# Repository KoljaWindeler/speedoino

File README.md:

# speedoino
A DIY Speedometer with OLED Display, GPS, Bluetooth, etc
Please refer to www.speedoino.de

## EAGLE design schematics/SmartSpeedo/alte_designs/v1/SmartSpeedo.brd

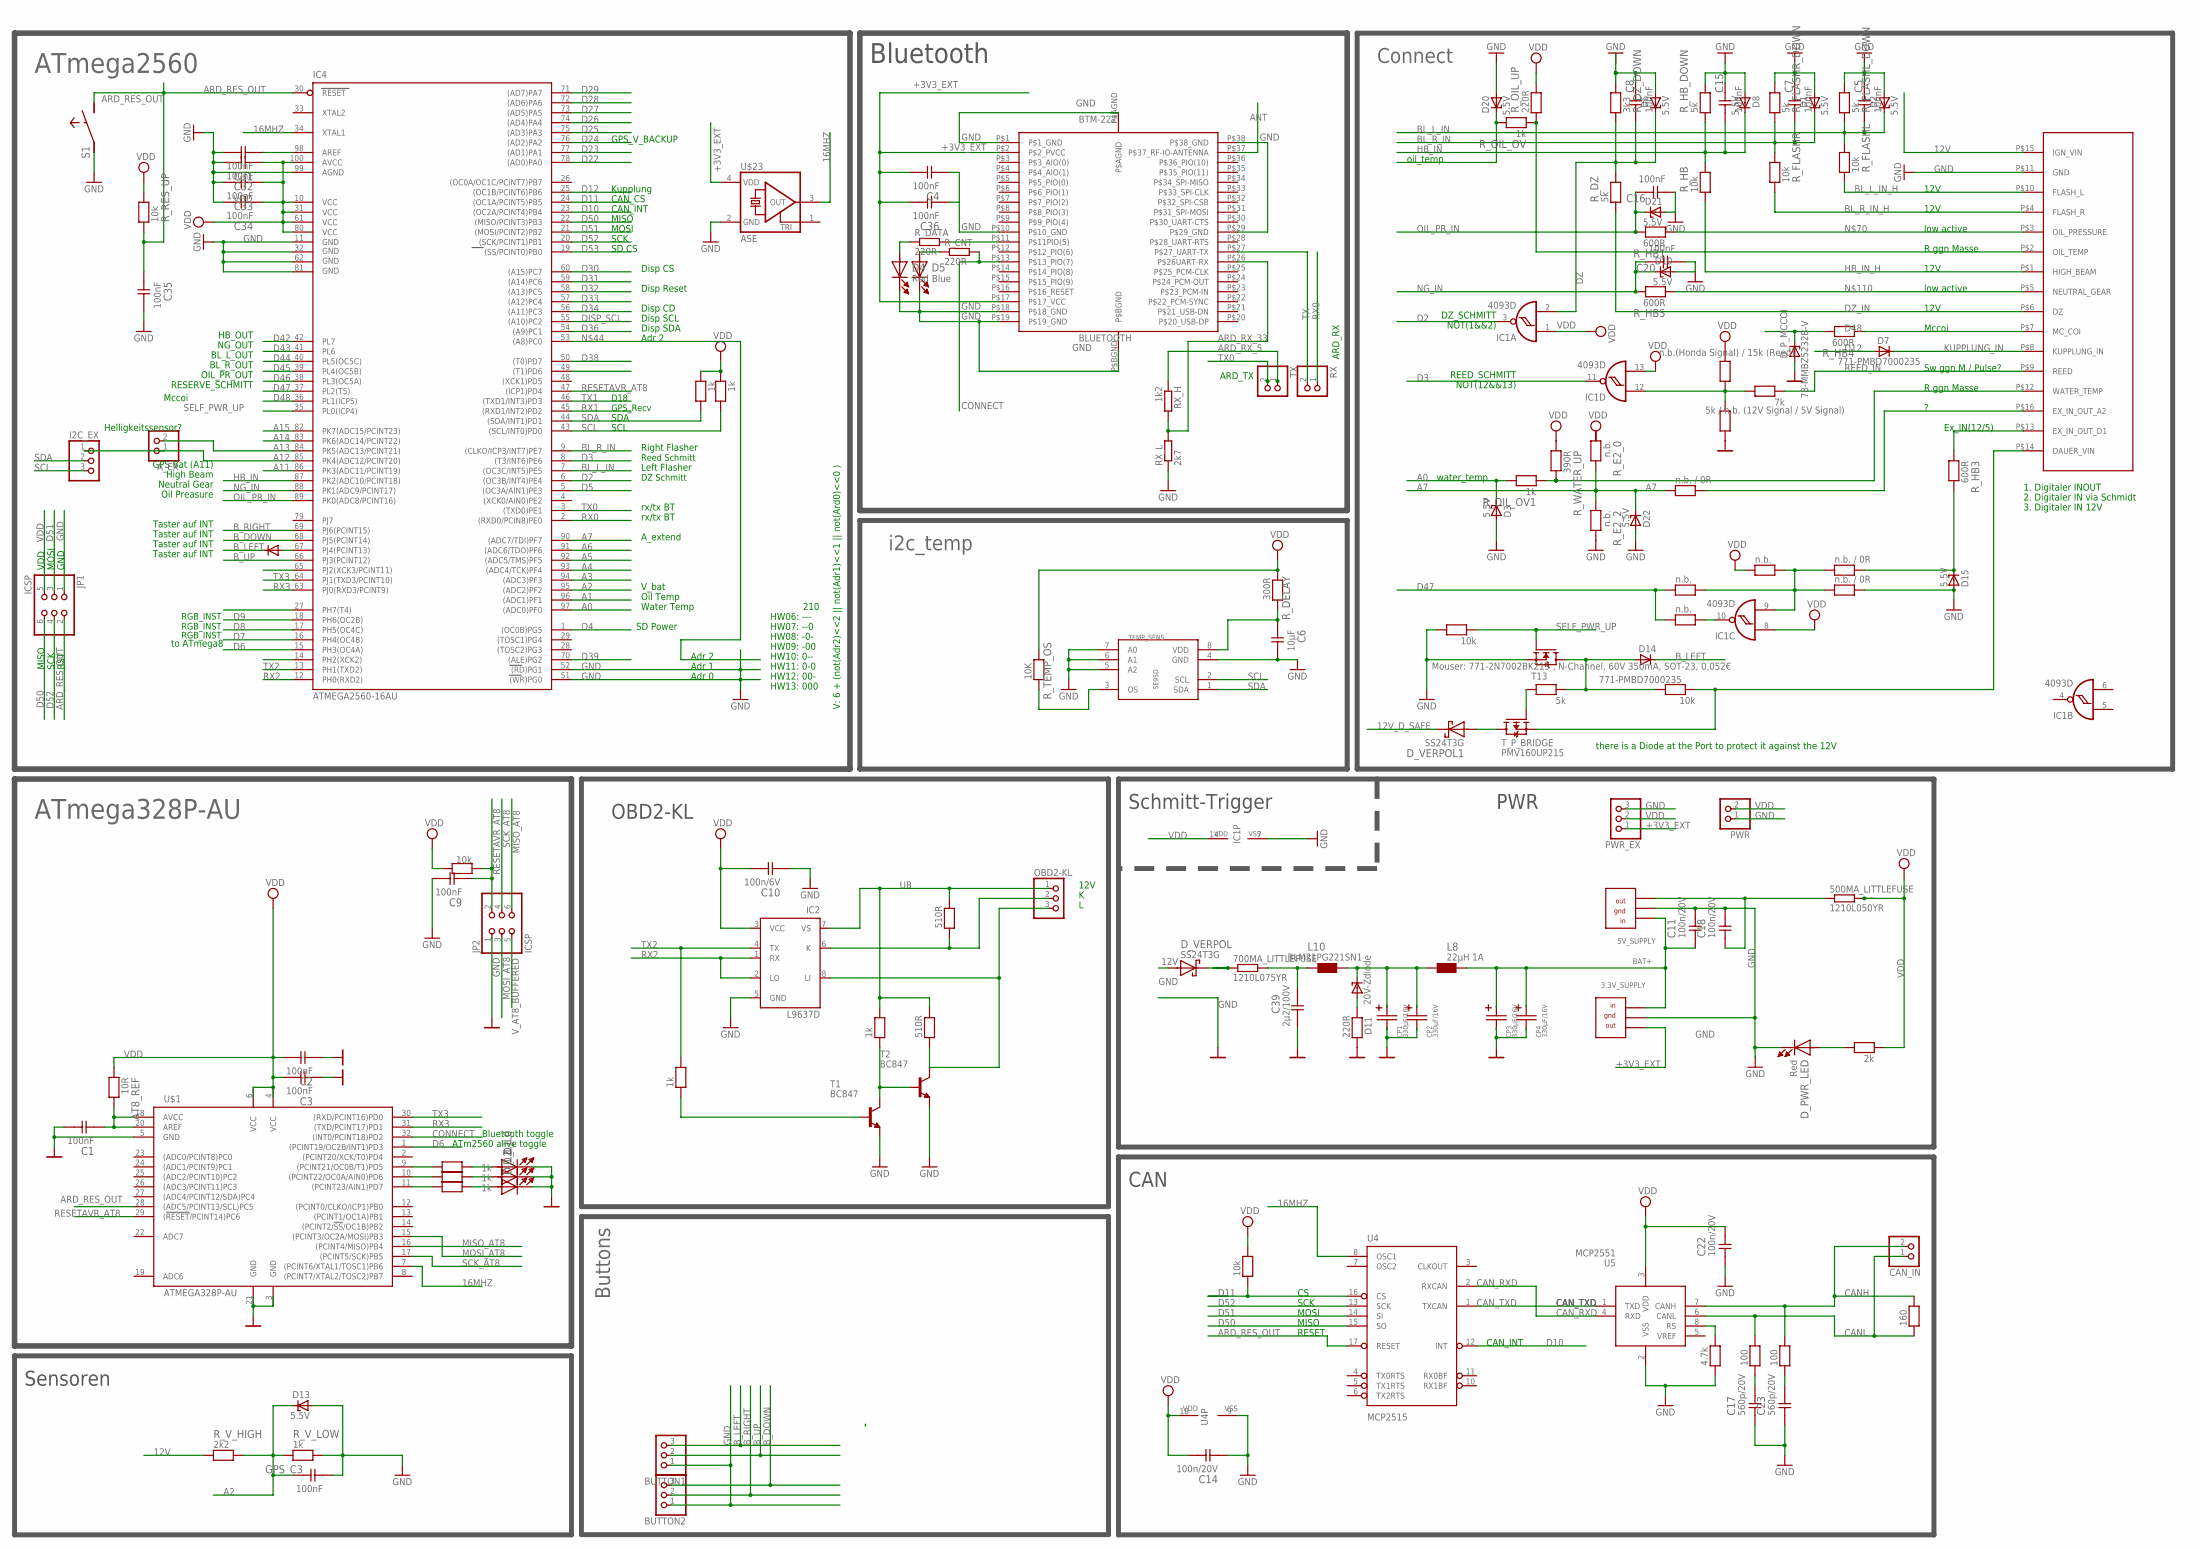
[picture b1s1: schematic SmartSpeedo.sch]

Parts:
3.3V_SUPPLY: OKI78SR3.31.5WHC; OKI-78SR
5V_SUPPLY: OKI78SR51.5W36HC; OKI-78SR
500MA_LITTLEFUSE: 1210L050YR; R1210
700MA_LITTLEFUSE: 1210L075YR; R1210
AT8_REF: 10R; 0805
A_EX: PINHD-1X2; 1X02
BLUETOOTH: BTM-222
BUTTON1, BUTTON2: PINHD-1X3; 1X03
C1, C2, C3, C4, C5, C7, C8, C9, C15, C16, C20, C31, C32, C33, C34, C35, C36: 100nF; 0805
C6: 10µF; 0805
C10: 100n/6V; 0805
C11, C14, C18, C22: 100n/20V; 0805
C17, C23: 560p/20V; 0805
C39: 2µ2/100V; 0805
CAN_IN: PINHD-1X2; 1X02
CP1, CP2, CP3, CP4: 330µF/16V; SMD/SMT_6.6/6.6
D1, D2, D3, D6, D8, D10, D13, D15, D20, D21, D22: 5.5V; SOT23
D4: Red; LED-0805
D5: Blue; LED-0805
D7, D12, D14: 771-PMBD7000235; SOT23
D11: 20V-Zdiode; SOT23
D_L0, D_L1, D_L2: LED0805; LED-0805
D_PWR_LED: Red; LED-0805
D_P_MCCOI: 78-MMBZ5232B-V; SOT23
D_VERPOL, D_VERPOL1: SS24T3G; SMB
GPS_C3: 100nF; 0805
I2C_EX: PINHD-1X3; 1X03
IC1: 4093D; SO14
IC2: L9637D; SO08
IC4: ATMEGA2560-16AU; TQFP100
JP1, JP2: ICSP; 2X03
K_PU: 510R; 0805
L8: 22µH 1A; L-PD54
L10: BLM21PG221SN1; 0805+603
OBD2-KL: PINHD-1X3; 1X03
PWR: PINHD-1X2; 1X02
PWR_EX: PINHD-1X3; 1X03
R1: 160; 0805
R2: 10k; 0805
R10, R12: 100; 0805
R13: 4.7k; 0805
RX: PINHD-1X2; 1X02
RX_H: 1k2; M0805
RX_L: 2k7; M0805
R_CNT: 220R; M0805
R_DATA: 220R; M0805
R_DEAKT_DAUER_P, R_DEAKT_DAUER_P1: 10k; 0805
R_DEAKT_DAUER_P2: 5k; 0805
R_DELAY: 300R; 0805
R_DZ: 5k; 0805
R_DZ_DOWN: 3k3; 0805
R_E1_0, R_E1_2, R_E1_4, R_E2_0, R_E2_2: n.b.; 0805
R_E1_1, R_E1_3, R_E2_1: n.b. / 0R; 0805
R_FLASHL: 10k; 0805
R_FLASHL_DOWN: 5k; 0805
R_FLASHR: 10k; 0805
R_FLASHR_DOWN: 5k; 0805
R_HB: 10k; 0805
R_HB1, R_HB3, R_HB4, R_HB5: 600R; 0805
R_HB_DOWN: 5k; 0805
R_L0, R_L1, R_L2: 1k; 0805
R_L3: 10k; 0805
R_LED_5V: 2k; 0805
R_OIL_OV, R_OIL_OV1: 1k; 0805
R_OIL_UP: 220R; 0805
R_REED: 7k; 0805
R_REED_DOWN: 5k / n.b. (12V Signal / 5V Signal); 0805
R_REED_UP: n.b.(Honda Signal) / 15k (Reed); 0805
R_RES_UP: 10k; 0805
R_R_LED_12: 220R; 0805
R_SCL_UP: 1k; 0805
R_SDA_UP: 1k; 0805
R_TEMP_OS: 10K; 0805
R_V_HIGH: 2k2; 0805
R_V_LOW: 1k; 0805
R_WATER_UP: 390R; 0805
S1: SW-TASTERECO-DIAGONAL; SW-ECO
SPEEDOSTECKER: SPEEDOSTECKER
T1, T2: BC847; SOT23
T13: Mouser: 771-2N7002BK215 , N-Channel, 60V 350mA, S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; SOT23
TEMP_SENS: SE95D; SOIC8
TX: PINHD-1X2; 1X02
TX_L, TX_L1: 1k; 0805
TX_L2: 510R; 0805
T_P_BRIDGE: PMV160UP215; SOT23
U4: MCP2515; SO-18W
U5: MCP2551; SO-08M
U$1: ATMEGA328P-AU; TQFP8
U$23: ASE

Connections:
12V: D_VERPOL.A, R_V_HIGH.1, SPEEDOSTECKER.P$15 (IGN_VIN)
12V_D_SAFE: 700MA_LITTLEFUSE.1, D_VERPOL.K, D_VERPOL1.K
12V_PERMANENT: R_DEAKT_DAUER_P.1, SPEEDOSTECKER.P$14 (DAUER_VIN), T_P_BRIDGE.2 (S)
12V_SAFE: 700MA_LITTLEFUSE.2, C39.1, L10.1
16MHZ: IC4.34 (XTAL1), U4.8 (OSC1), U$1.7 ((PCINT6/XTAL1/TOSC1)PB6), U$23.3 (OUT)
+3V3_EXT: 3.3V_SUPPLY.OUT, BLUETOOTH.P$2 (P$2_PVCC), BLUETOOTH.P$17 (P$17_VCC), C4.2, C36.2, PWR_EX.1
A0: D3.3 (C), IC4.97 ((ADC0)PF0), R_OIL_OV1.2
A1: D20.3 (C), IC4.96 ((ADC1)PF1), R_OIL_OV.2
A2: D13.3 (C), GPS_C3.2, IC4.95 ((ADC2)PF2), R_V_HIGH.2, R_V_LOW.1
A3: IC4.94 ((ADC3)PF3)
A4: IC4.93 ((ADC4/TCK)PF4)
A5: IC4.92 ((ADC5/TMS)PF5)
A6: IC4.91 ((ADC6/TDO)PF6)
A7: D22.3 (C), IC4.90 ((ADC7/TDI)PF7), R_E2_0.2, R_E2_1.2, R_E2_2.1
A11: IC4.86 (PK3(ADC11/PCINT19))
A12: A_EX.1, I2C_EX.1, IC4.85 (PK4(ADC12/PCINT20))
A13: A_EX.2, IC4.84 (PK5(ADC13/PCINT21))
A14: IC4.83 (PK6(ADC14/PCINT22))
A15: IC4.82 (PK7(ADC15/PCINT23))
ANT: BLUETOOTH.P$37 (P$37_RF-IO-ANTENNA)
ARD_RES_OUT: C35.1, IC4.30 (RESET), JP1.2, R_RES_UP.1, S1.4 (2), U4.17 (RESET), U$1.28 ((ADC5/PCINT13/SCL)PC5)
ARD_RX_5: RX_H.1, TX.1
ARD_RX_33: BLUETOOTH.P$26 (P$26UART-RX), RX_H.2, RX_L.2
BAT+: 3.3V_SUPPLY.IN, 5V_SUPPLY.IN, C11.1, CP3.POS (PLUS), CP4.POS (PLUS), L8.2
BL_L_IN: C5.1, D2.3 (C), IC4.7 ((OC3C/INT5)PE5), R_FLASHL.2, R_FLASHL_DOWN.1
BL_L_IN_H: R_FLASHL.1, SPEEDOSTECKER.P$10 (FLASH_L)
BL_R_IN: C7.1, D1.3 (C), IC4.9 ((CLKO/ICP3/INT7)PE7), R_FLASHR.2, R_FLASHR_DOWN.1
BL_R_IN_H: R_FLASHR.1, SPEEDOSTECKER.P$4 (FLASH_R)
B_DOWN: BUTTON2.3, IC4.68 (PJ5(PCINT14))
B_LEFT: BUTTON1.3, D12.3 (C), D14.3 (C)
B_RIGHT: BUTTON2.2, IC4.69 (PJ6(PCINT15))
B_UP: BUTTON1.2, IC4.66 (PJ3(PCINT12))
CANH: CAN_IN.2, R1.2, R12.2, U5.7 (CANH)
CANL: CAN_IN.1, R1.1, R10.2, U5.6 (CANL)
CAN_RXD: U4.2 (RXCAN), U5.4 (RXD)
CAN_TXD: U4.1 (TXCAN), U5.1 (TXD)
CONNECT: BLUETOOTH.P$13 (P$13_PIO(7)), R_CNT.2, U$1.32 ((INT0/PCINT18)PD2)
D2: IC1.3 (O), IC4.6 ((OC3B/INT4)PE4)
D3: IC1.11 (O), IC4.8 ((T3/INT6)PE6)
D4: IC4.1 ((OC0B)PG5)
D5: IC4.5 ((OC3A/AIN1)PE3)
D6: IC4.15 (PH3(OC4A)), U$1.1 ((PCINT19/OC2B/INT1)PD3)
D7: IC4.16 (PH4(OC4B))
D8: IC4.17 (PH5(OC4C))
D9: IC4.18 (PH6(OC2B))
D10: IC4.23 ((OC2A/PCINT4)PB4), U4.12 (INT)
D11: IC4.24 ((OC1A/PCINT5)PB5), R2.1, U4.16 (CS)
D12: D7.1 (A), IC4.25 ((OC1B/PCINT6)PB6)
D22: IC4.78 ((AD0)PA0)
D23: IC4.77 ((AD1)PA1)
D24: IC4.76 ((AD2)PA2)
D25: IC4.75 ((AD3)PA3)
D26: IC4.74 ((AD4)PA4)
D27: IC4.73 ((AD5)PA5)
D28: IC4.72 ((AD6)PA6)
D29: IC4.71 ((AD7)PA7)
D30: IC4.60 ((A15)PC7)
D31: IC4.59 ((A14)PC6)
D32: IC4.58 ((A13)PC5)
D33: IC4.57 ((A12)PC4)
D34: IC4.56 ((A11)PC3)
D36: IC4.54 ((A9)PC1)
D38: IC4.50 ((T0)PD7)
D39: IC4.70 ((ALE)PG2)
D42: IC4.42 (PL7)
D43: IC4.41 (PL6)
D44: IC4.40 (PL5(OC5C))
D45: IC4.39 (PL4(OC5B))
D46: IC4.38 (PL3(OC5A))
D47: IC4.37 (PL2(T5)), R_E1_2.2, R_E1_4.2
D48: D_P_MCCOI.3 (C), IC4.36 (PL1(ICP5)), R_HB4.2
D50: IC4.22 ((MISO/PCINT3)PB3), JP1.6, U4.15 (SO)
D51: IC4.21 ((MOSI/PCINT2)PB2), JP1.3, U4.14 (SI)
D52: IC4.20 ((SCK/PCINT1)PB1), JP1.4, U4.13 (SCK)
D53: IC4.19 ((SS/PCINT0)PB0)
DISP_SCL: IC4.55 ((A10)PC2)
DZ: C8.1, D6.3 (C), IC1.2 (I1), R_DZ.2, R_DZ_DOWN.1
DZ_IN: R_DZ.1, SPEEDOSTECKER.P$6 (DZ)
GND: 3.3V_SUPPLY.GND, 5V_SUPPLY.GND, BLUETOOTH.P$1 (P$1_GND), BLUETOOTH.P$10 (P$10_GND), BLUETOOTH.P$18 (P$18_GND), BLUETOOTH.P$19 (P$19_GND), BLUETOOTH.P$29 (P$29_GND), BLUETOOTH.P$38 (P$38_GND), BLUETOOTH.P$AGND, BLUETOOTH.P$BGND, BUTTON1.1, BUTTON2.1, C1.2, C2.1, C3.1, C4.1, C5.2, C6.2, C7.2, C8.2, C9.2, C10.1, C11.2, C14.1, C15.2, C16.1, C17.1, C18.2, C20.1, C22.1, C23.1, C31.2, C32.2, C33.2, C34.2, C35.2, C36.1, C39.2, CP1.NEG (GND), CP2.NEG (GND), CP3.NEG (GND), CP4.NEG (GND), D1.1 (A), D2.1 (A), D3.1 (A), D4.2 (K), D5.2 (K), D6.1 (A), D8.1 (A), D10.1 (A), D13.1 (A), D15.1 (A), D20.1 (A), D21.1 (A), D22.1 (A), D_L0.2 (K), D_L1.2 (K), D_L2.2 (K), D_PWR_LED.2 (K), D_P_MCCOI.1 (A), GPS_C3.1, IC1.7 (VSS), IC2.5 (GND), IC4.11 (GND), IC4.32 (GND1), IC4.51 ((WR)PG0), IC4.52 ((RD)PG1), IC4.62 (GND2), IC4.81 (GND3), IC4.99 (AGND), JP1.1, JP2.1, PWR.1, PWR_EX.3, R13.1, RX_L.1, R_DEAKT_DAUER_P1.2, R_DZ_DOWN.2, R_E1_3.1, R_E2_2.2, R_FLASHL_DOWN.2, R_FLASHR_DOWN.2, R_HB_DOWN.2, R_REED_DOWN.2, R_R_LED_12.1, R_V_LOW.2, S1.1, SPEEDOSTECKER.P$11 (GND), T1.2 (E), T2.2 (E), T13.2 (S), TEMP_SENS.4 (GND), TEMP_SENS.5 (A2), TEMP_SENS.6 (A1), TEMP_SENS.7 (A0), U4.9 (VSS), U5.2 (VSS), U$1.3 (GND), U$1.5 (GND), U$1.21 (GND), U$23.2 (GND)
HB_IN: C15.1, D8.3 (C), IC4.87 (PK2(ADC10/PCINT18)), R_HB.2, R_HB_DOWN.1
HB_IN_H: R_HB.1, SPEEDOSTECKER.P$1 (HIGH_BEAM)
KUPPLUNG_IN: D7.3 (C), SPEEDOSTECKER.P$8 (KUPPLUNG_IN)
MISO_AT8: JP2.6, U$1.16 ((PCINT4/MISO)PB4)
MOSI_AT8: JP2.3, U$1.15 ((PCINT3/OC2A/MOSI)PB3)
N999: R_OIL_OV.1, R_OIL_UP.1, SPEEDOSTECKER.P$2 (OIL_TEMP)
unnamed: CP1.POS (PLUS), CP2.POS (PLUS), D11.3 (C), L8.1, L10.2
unnamed: AT8_REF.2, C1.1, U$1.18 (AVCC), U$1.20 (AREF)
unnamed: C6.1, R_DELAY.1, TEMP_SENS.8 (VDD)
unnamed: D5.1 (A), R_CNT.1
unnamed: IC2.6 (K), K_PU.1, OBD2-KL.2
unnamed: T1.3 (C), T2.1 (B), TX_L1.1
unnamed: T1.1 (B), TX_L.1
unnamed: D_PWR_LED.1 (A), R_LED_5V.2
unnamed: IC2.8 (LI), OBD2-KL.3, T2.3 (C), TX_L2.1
unnamed: D4.1 (A), R_DATA.1
unnamed: R_L2.1, U$1.11 ((PCINT23/AIN1)PD7)
unnamed: R_L1.1, U$1.10 ((PCINT22/OC0A/AIN0)PD6)
unnamed: 5V_SUPPLY.OUT, 500MA_LITTLEFUSE.1, C18.1
unnamed: R_L0.1, U$1.9 ((PCINT21/OC0B/T1)PD5)
unnamed: R_DEAKT_DAUER_P2.2, T_P_BRIDGE.1 (G)
unnamed: C31.1, IC4.98 (AREF)
unnamed: IC1.9 (I1), R_E1_0.1, R_E1_1.2, R_E1_2.1, R_E1_3.2
unnamed: IC1.10 (O), R_E1_4.1
unnamed: D12.1 (A), IC4.67 (PJ4(PCINT13))
unnamed: R_HB3.1, SPEEDOSTECKER.P$13 (EX_IN_OUT_D1)
unnamed: R_E2_1.1, SPEEDOSTECKER.P$16 (EX_IN_OUT_A2)
unnamed: D_VERPOL1.A, T_P_BRIDGE.3 (D)
unnamed: C17.2, R10.1
unnamed: R_HB1.1, SPEEDOSTECKER.P$3 (OIL_PRESSURE)
unnamed: C23.2, R12.1
unnamed: D15.3 (C), R_E1_1.1, R_HB3.2
unnamed: R_TEMP_OS.1, TEMP_SENS.3 (OS)
unnamed: R_HB4.1, SPEEDOSTECKER.P$7 (MC_COI)
unnamed: D11.1 (A), R_R_LED_12.2
unnamed: R_HB5.1, SPEEDOSTECKER.P$5 (NEUTRAL_GEAR)
unnamed: R_OIL_OV1.1, R_WATER_UP.2, SPEEDOSTECKER.P$12 (WATER_TEMP)
unnamed: R13.2, U5.8 (RS)
NET12: D14.1 (A), R_DEAKT_DAUER_P.2, R_DEAKT_DAUER_P2.1, T13.3 (D)
NG_IN: C20.2, D10.3 (C), IC4.88 (PK1(ADC9/PCINT17)), R_HB5.2
OIL_PR_IN: C16.2, D21.3 (C), IC4.89 (PK0(ADC8/PCINT16)), R_HB1.2
P0: D_L0.1 (A), R_L0.2
P1: D_L1.1 (A), R_L1.2
P2: D_L2.1 (A), R_L2.2
REED: IC1.12 (I0), R_REED.2, R_REED_DOWN.1, R_REED_UP.2
REED_IN: R_REED.1, SPEEDOSTECKER.P$9 (REED)
RESETAVR_AT8: C9.1, IC4.47 ((ICP1)PD4), JP2.2, R_L3.2, U$1.29 ((!RESET!/PCINT14)PC6)
RX0: IC4.2 ((RXD0/PCIN8)PE0), RX.1
RX1: IC4.45 ((RXD1/INT2)PD2)
RX2: IC2.1 (RX), IC2.2 (LO), IC4.12 (PH0(RXD2))
RX3: IC4.63 (PJ0(RXD3/PCINT9)), U$1.31 ((TXD/PCINT17)PD1)
SCK_AT8: JP2.4, U$1.17 ((PCINT5/SCK)PB5)
SCL: I2C_EX.3, IC4.43 ((SCL/INT0)PD0), R_SCL_UP.2, TEMP_SENS.2 (SCL)
SDA: I2C_EX.2, IC4.44 ((SDA/INT1)PD1), R_SDA_UP.2, TEMP_SENS.1 (SDA)
SELF_PWR_UP: IC4.35 (PL0(ICP4)), R_DEAKT_DAUER_P1.1, T13.1 (G)
TO_DATA_LED: BLUETOOTH.P$11 (P$11PIO(5)), R_DATA.2
TX: BLUETOOTH.P$27 (P$27_UART-TX), RX.2
TX0: IC4.3 ((TXD0)PE1), TX.2
TX1: IC4.46 ((TXD1/INT3)PD3)
TX2: IC2.4 (TX), IC4.13 (PH1(TXD2)), TX_L.2
TX3: IC4.64 (PJ1(TXD3/PCINT10)), U$1.30 ((RXD/PCINT16)PD0)
UB: IC2.7 (VS), K_PU.2, OBD2-KL.1, TX_L1.2, TX_L2.2
VDD: 500MA_LITTLEFUSE.2, AT8_REF.1, C2.2, C3.2, C10.2, C14.2, C22.2, C32.1, C33.1, C34.1, IC1.1 (I0), IC1.8 (I0), IC1.13 (I1), IC1.14 (VDD), IC2.3 (VCC), IC4.10 (VCC), IC4.31 (VCC1), IC4.61 (VCC2), IC4.80 (VCC3), IC4.100 (AVCC), JP1.5, PWR.2, PWR_EX.2, R2.2, R_DELAY.2, R_E1_0.2, R_L3.1, R_LED_5V.1, R_OIL_UP.2, R_REED_UP.1, R_RES_UP.2, R_SCL_UP.1, R_SDA_UP.1, R_TEMP_OS.2, R_WATER_UP.1, U4.18 (VDD), U5.3 (VDD), U$1.4 (VCC), U$1.6 (VCC), U$23.4 (VDD)
V_AT8_BUFFERED: JP2.5

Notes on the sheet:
Schmitt-Trigger
PWR
Sensoren
Bluetooth
Buttons
MOSI
SCK
MISO
SDA
SCL
DZ_SCHMITT
REED_SCHMITT
oil_temp
ATmega2560
D18
GND
VDD
RST
ARD_RX
ARD_TX
i2c_temp
RGB_INST
Reed Schmitt
DZ Schmitt
GPS_Recv
Oil Temp
rx/tx BT
Disp SDA
Disp SCL
Disp CD
Disp CS
SD CS
Water Temp
V_bat
RESERVE_SCHMITT
Mccoi
Kupplung
Ex_IN(12/5)
SD Power
Disp Reset

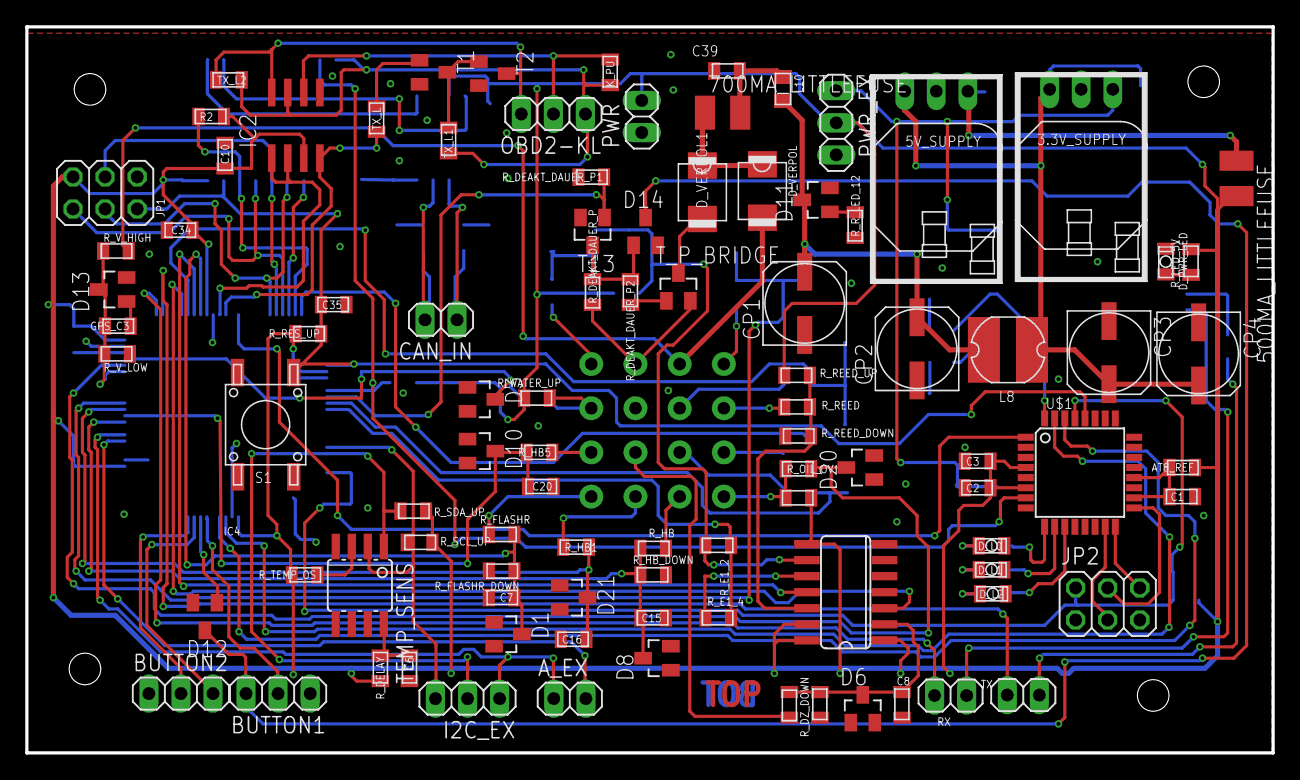
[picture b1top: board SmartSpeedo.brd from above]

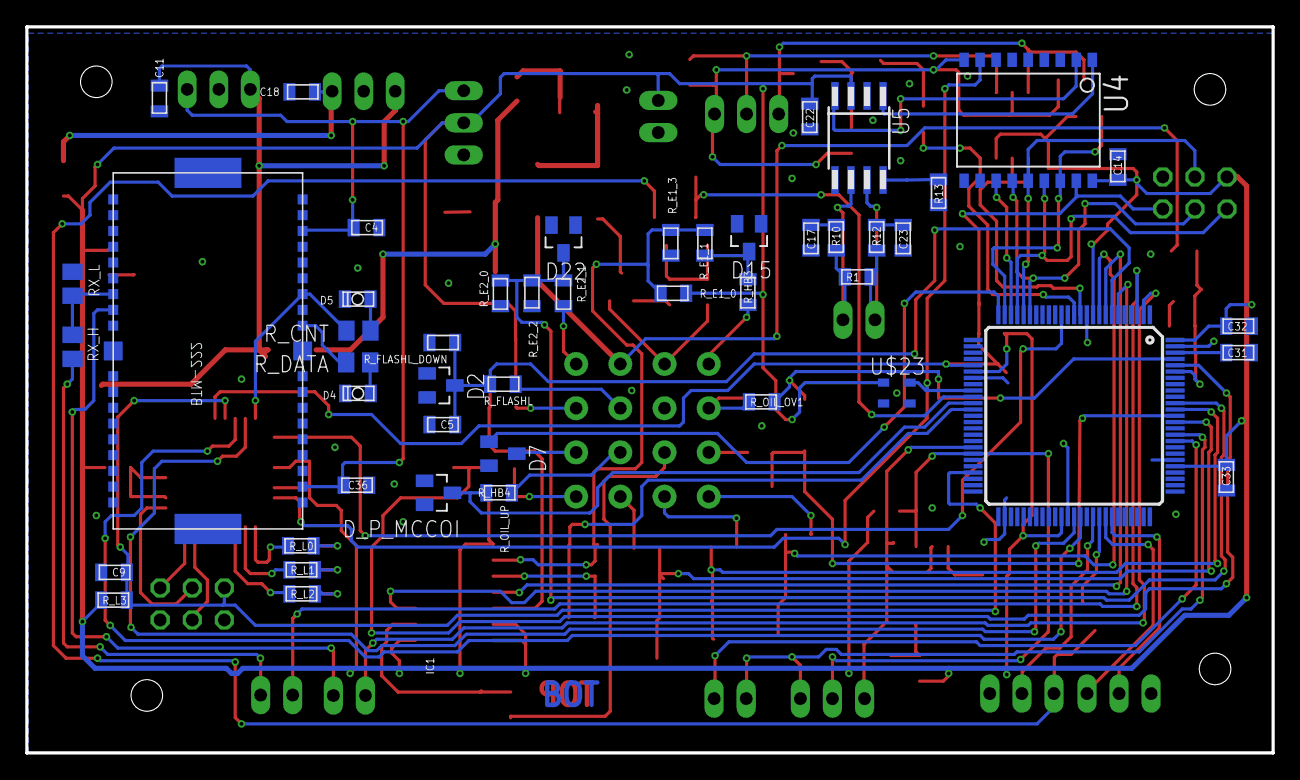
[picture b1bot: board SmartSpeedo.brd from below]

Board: 4 copper layers, 98.7 x 57.5 mm, 145 parts (48 on the bottom side), 104 nets.

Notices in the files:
ATm2560Bootloader/stk500boot.c:
License: GNU General Public License
LICENSE:
Copyright (C) 2006 Peter Fleury
Firmware/inc/pins_arduino.c:
Copyright (c) 2005 David A. Mellis
Public License along with this library; if not, write to the
Free Software Foundation, Inc., 59 Temple Place, Suite 330,
Boston, MA  02111-1307  USA
parts and their libraries:
STM32F407Vx_LQFP100: Copyright 2012 by Ersan Günes, Quantitec, info@quantitec.de
